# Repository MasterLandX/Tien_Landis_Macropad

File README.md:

# Tien_Landis_Macropad
My Macropad design using 5 keys along with a rotary encoder.

### Specifications

BOM: 
- 5x Kalih Box Jade Switches
- 1x EC11 Rotary Encoder
- 2x SK6812 MINI Leds
- 1x XIAO RP2040
- 5x Blank DSA Keycaps
- 4x M3x16 Bolt
- 4x M3 Heatset

Others:
- KMK Firmware
- Top Case.stl 
- Bottom Case.stl

Schematic            |  PCB         |   Case
:-------------------------:|:-------------------------:|:-------------------------:|
    |    |

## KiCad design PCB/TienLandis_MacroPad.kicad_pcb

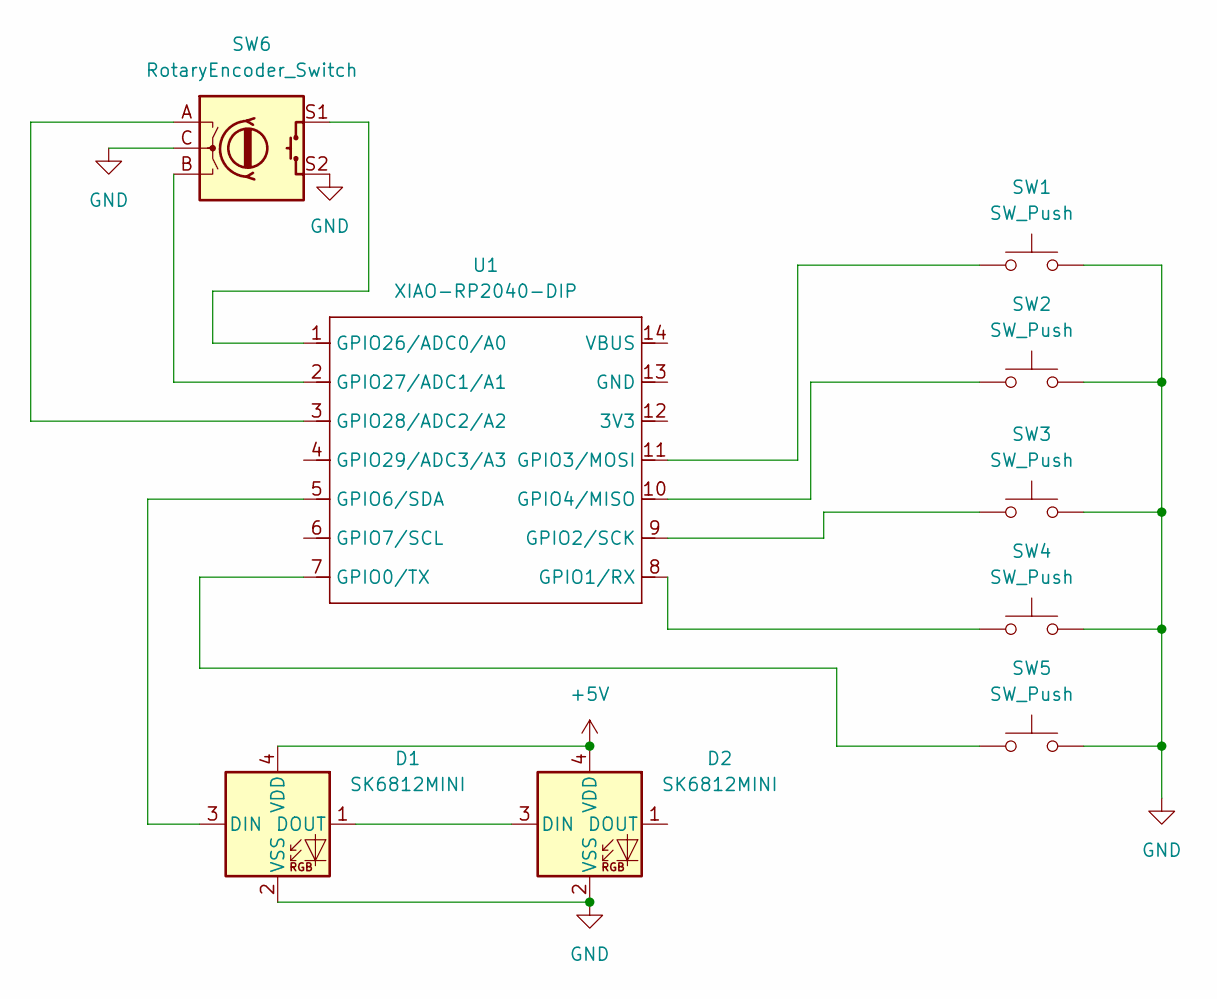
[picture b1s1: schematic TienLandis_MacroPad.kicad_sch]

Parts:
D1, D2: SK6812MINI; LED_SK6812MINI_PLCC4_3.5x3.5mm_P1.75mm
SW1, SW2, SW3, SW4, SW5: SW_Push; SW_Cherry_MX_1.00u_PCB
SW6: RotaryEncoder_Switch; RotaryEncoder_Alps_EC11E-Switch_Vertical_H20mm
U1: XIAO-RP2040-DIP

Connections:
+5V: D1.4 (VDD), D2.4 (VDD)
GND: D1.2 (VSS), D2.2 (VSS), SW1.2, SW2.2, SW3.2, SW4.2, SW5.2, SW6.C, SW6.S2
unnamed: D1.3 (DIN), U1.5 (GPIO6/SDA)
unnamed: D1.1 (DOUT), D2.3 (DIN)
unnamed: SW5.1, U1.7 (GPIO0/TX)
unnamed: SW4.1, U1.8 (GPIO1/RX)
unnamed: SW3.1, U1.9 (GPIO2/SCK)
unnamed: SW1.1, U1.11 (GPIO3/MOSI)
unnamed: SW2.1, U1.10 (GPIO4/MISO)
unnamed: SW6.S1, U1.1 (GPIO26/ADC0/A0)
unnamed: SW6.B, U1.2 (GPIO27/ADC1/A1)
unnamed: SW6.A, U1.3 (GPIO28/ADC2/A2)

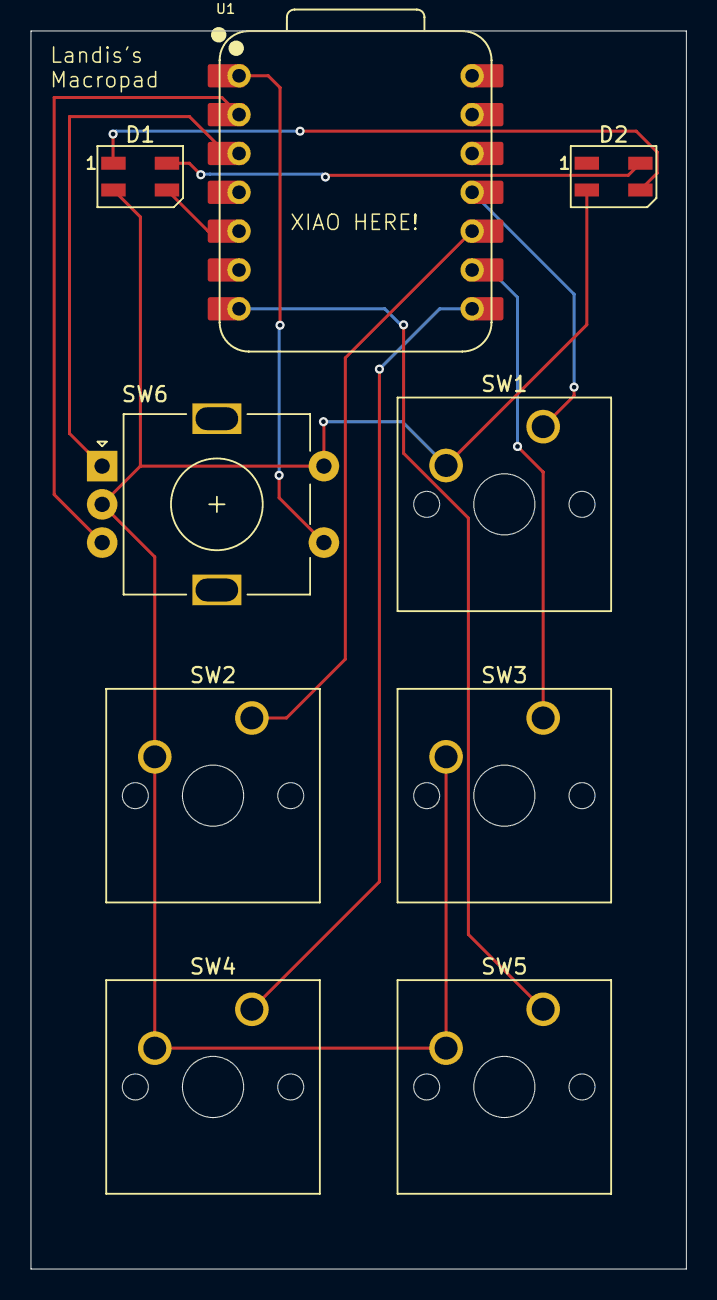
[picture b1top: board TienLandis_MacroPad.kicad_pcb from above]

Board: 2 copper layers, 42.9 x 81.0 mm, 9 parts (0 on the bottom side), 12 nets.

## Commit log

2025-12-23 Create CAD folder
2025-12-23 Create temp
